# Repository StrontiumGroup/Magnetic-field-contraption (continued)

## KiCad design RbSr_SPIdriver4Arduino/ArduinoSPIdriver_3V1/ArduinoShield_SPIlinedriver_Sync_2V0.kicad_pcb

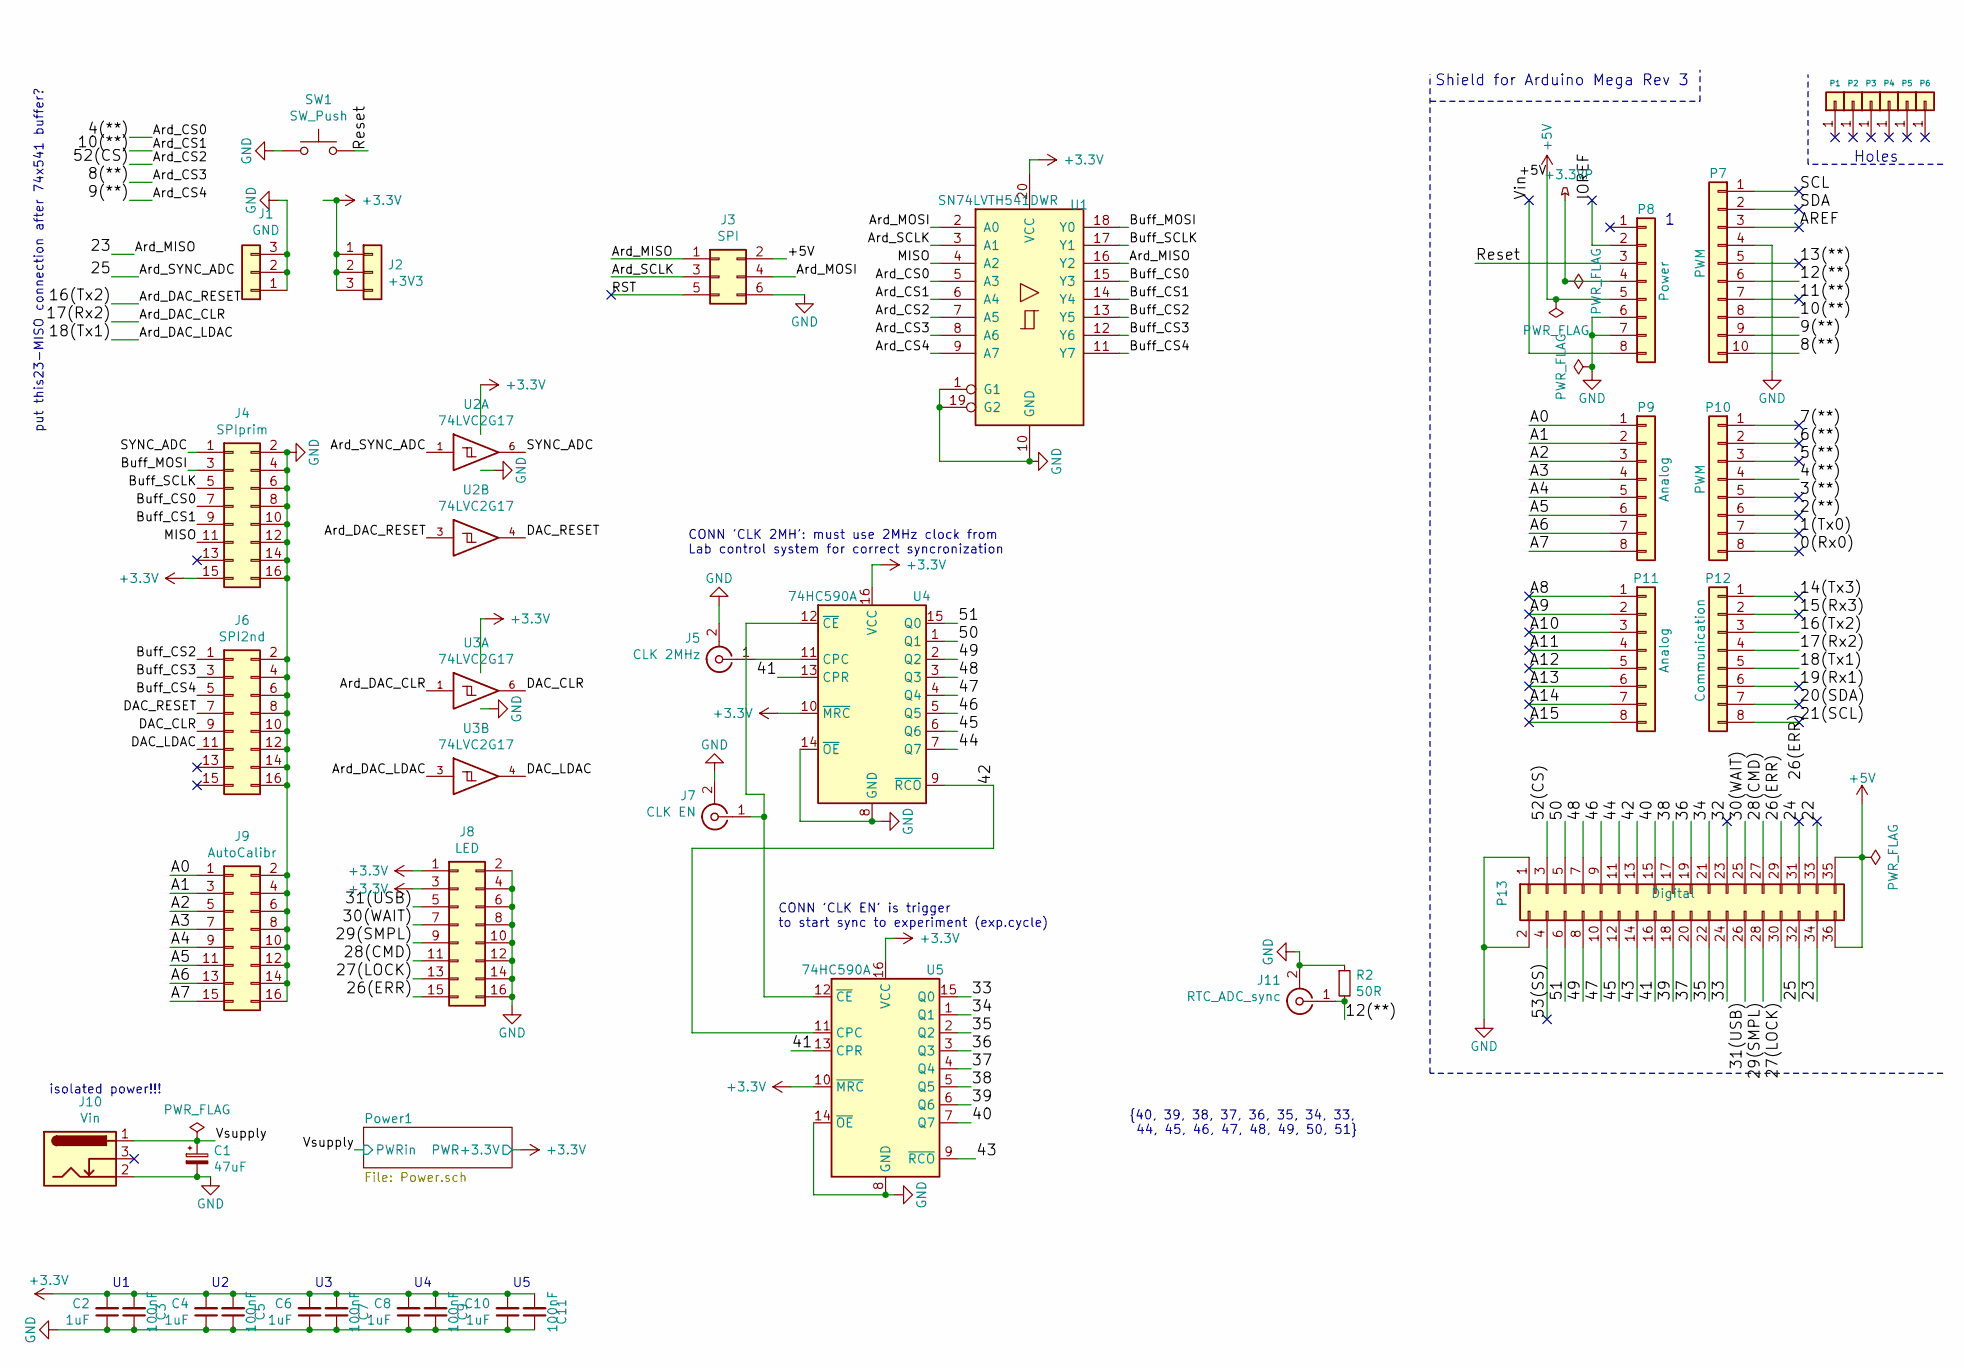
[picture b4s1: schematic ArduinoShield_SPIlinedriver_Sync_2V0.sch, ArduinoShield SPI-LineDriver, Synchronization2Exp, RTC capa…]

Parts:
C1: 47uF; CP_EIA-7343-30_AVX-N; DigiKey 490-ECASD31C476M040KA0CT-ND
C2, C4, C6, C8, C10: 1uF; C_0603_1608Metric; DigiKey 732-7971-1-ND
C3, C5, C7, C9, C11: 100nF; C_0603_1608Metric; DigiKey 732-7989-1-ND
J1: GND; PinSocket_1x03_P2.54mm_Vertical; DigiKey SAM1213-03-ND
J2: +3V3; PinSocket_1x03_P2.54mm_Vertical; DigiKey SAM1213-03-ND
J3: SPI; PinSocket_2x03_P2.54mm_Vertical; DigiKey SAM1204-03-ND
J4: SPIprim; IDC-Header_2x08_P2.54mm_Vertical; DigiKey 609-3641-ND
J5: CLK 2MHz; SMA_Amphenol_132291_Vertical; DigiKey ACX1976-ND
J6: SPI2nd; IDC-Header_2x08_P2.54mm_Vertical; DigiKey 609-3641-ND
J7: CLK EN; SMA_Amphenol_132291_Vertical; DigiKey ACX1976-ND
J8: LED; IDC-Header_2x08_P2.54mm_Vertical; DigiKey 609-3641-ND
J9: AutoCalibr; IDC-Header_2x08_P2.54mm_Vertical; DigiKey 609-3641-ND
J10: Vin; BarrelJack_Wuerth_6941xx301002; DigiKey 732-5930-ND
J11: RTC_ADC_sync; SMA_Amphenol_132291_Vertical; DigiKey ACX1976-ND
P1, P2, P3, P4, P5, P6: CONN_01X01; Arduino_1pin
P7: PWM; Socket_Strip_Arduino_1x10; DigiKey SAM1206-10-ND
P8: Power; Socket_Strip_Arduino_1x08; DigiKey SAM11912-ND
P9, P11: Analog; Socket_Strip_Arduino_1x08; DigiKey SAM11912-ND
P10: PWM; Socket_Strip_Arduino_1x08; DigiKey SAM11912-ND
P12: Communication; Socket_Strip_Arduino_1x08; DigiKey SAM11912-ND
P13: Digital; Socket_Strip_Arduino_2x18; DigiKey SAM1204-18-ND
R2: 50R; R_0603_1608Metric; DigiKey 541-2655-1-ND
SW1: SW_Push; WS-TASV_SwitchTactile_430471035826; DigiKey 430471035826
U1: SN74LVTH541DWR; TSSOP-20_4.4x6.5mm_P0.65mm; DigiKey 296-8729-1-ND
U2, U3: 74LVC2G17; SOT-363_SC-70-6; DigiKey 296-13013-1-ND
U4, U5: 74HC590A; SOIC-16_3.9x9.9mm_P1.27mm; DigiKey 296-17132-1-ND

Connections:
+3.3VP: P8.4
+3V3: C2.2, C3.2, C4.2, C5.2, C6.2, C7.2, C8.2, C9.2, C10.2, C11.2, J2.1, J2.2, J2.3, J4.15, J8.1, J8.3, U1.20 (VCC), U2.5 (VCC), U3.5 (VCC), U4.10 (~MRC), U4.16 (VCC), U5.10 (~MRC), U5.16 (VCC); also elsewhere on the board
+5V: J3.2, P8.5, P13.35, P13.36
/0(Rx0): P10.8
/1(Tx0): P10.7
/2(**): P10.6
/3(**): P10.5
/4(**): P10.4, U1.5 (A3)
/5(**): P10.3
/6(**): P10.2
/7(**): P10.1
/8(**): P7.10, U1.8 (A6)
/9(**): P7.9, U1.9 (A7)
/10(**): P7.8, U1.6 (A4)
/11(**): P7.7
/12(**): J11.1 (In), P7.6, R2.2
/13(**): P7.5
/14(Tx3): P12.1
/15(Rx3): P12.2
/16(Tx2): P12.3, U2.3
/17(Rx2): P12.4, U3.1
/18(Tx1): P12.5, U3.3
/19(Rx1): P12.6
/20(SDA): P12.7
/21(SCL): P12.8
/22: P13.33
/23: J3.1, P13.34, U1.16 (Y2)
/24: P13.31
/25: P13.32, U2.1
/26(ERR): J8.15, P13.29
/27(LOCK): J8.13, P13.30
/28(CMD): J8.11, P13.27
/29(SMPL): J8.9, P13.28
/30(WAIT): J8.7, P13.25
/31(USB): J8.5, P13.26
/32: P13.23
/33: P13.24, U5.15 (Q0)
/34: P13.21, U5.1 (Q1)
/35: P13.22, U5.2 (Q2)
/36: P13.19, U5.3 (Q3)
/37: P13.20, U5.4 (Q4)
/38: P13.17, U5.5 (Q5)
/39: P13.18, U5.6 (Q6)
/40: P13.15, U5.7 (Q7)
/41: P13.16, U4.13 (CPR), U5.13 (CPR)
/42: P13.13, U4.9 (~RCO), U5.11 (CPC)
/43: P13.14, U5.9 (~RCO)
/44: P13.11, U4.7 (Q7)
/45: P13.12, U4.6 (Q6)
/46: P13.9, U4.5 (Q5)
/47: P13.10, U4.4 (Q4)
/48: P13.7, U4.3 (Q3)
/49: P13.8, U4.2 (Q2)
/50: P13.5, U4.1 (Q1)
/51: P13.6, U4.15 (Q0)
/52(CS): P13.3, U1.7 (A5)
/53(SS): P13.4
/A0: J9.1, P9.1
/A1: J9.3, P9.2
/A2: J9.5, P9.3
/A3: J9.7, P9.4
/A4: J9.9, P9.5
/A5: J9.11, P9.6
/A6: J9.13, P9.7
/A7: J9.15, P9.8
/A8: P11.1
/A9: P11.2
/A10: P11.3
/A11: P11.4
/A12: P11.5
/A13: P11.6
/A14: P11.7
/A15: P11.8
/AREF: P7.3
/Ard_MOSI: J3.4, U1.2 (A0)
/Ard_SCLK: J3.3, U1.3 (A1)
/Buff_CS0: J4.7, U1.15 (Y3)
/Buff_CS1: J4.9, U1.14 (Y4)
/Buff_CS2: J6.1, U1.13 (Y5)
/Buff_CS3: J6.3, U1.12 (Y6)
/Buff_CS4: J6.5, U1.11 (Y7)
/Buff_MOSI: J4.3, U1.18 (Y0)
/Buff_SCLK: J4.5, U1.17 (Y1)
/DAC_CLR: J6.9, U3.6
/DAC_LDAC: J6.11, U3.4
/DAC_RESET: J6.7, U2.4
/IOREF: P8.2
/MISO: J4.11, U1.4 (A2)
/RST: J3.5
/Reset: P8.3, SW1.2
/SCL: P7.1
/SDA: P7.2
/SYNC_ADC: J4.1, U2.6
/Vin: P8.8
/Vsupply: C1.1, J10.1; also elsewhere on the board
GND: C1.2, C2.1, C3.1, C4.1, C5.1, C6.1, C7.1, C8.1, C9.1, C10.1, C11.1, J1.1, J1.2, J1.3, J3.6, J4.2, J4.4, J4.6, J4.8, J4.10, J4.12, J4.14, J4.16, J5.2 (Ext), J6.2, J6.4, J6.6, J6.8, J6.10, J6.12, J6.14, J6.16, J7.2 (Ext), J8.2, J8.4, J8.6, J8.8, J8.10, J8.12, J8.14, J8.16, J9.2, J9.4, J9.6, J9.8, J9.10, J9.12, J9.14, J9.16, J10.2, J11.2 (Ext), P7.4, P8.6, P8.7, P13.1, P13.2, R2.1, SW1.1, U1.1 (G1), U1.10 (GND), U1.19 (G2), U2.2 (GND), U3.2 (GND), U4.8 (GND), U4.14 (~OE), U5.8 (GND), U5.14 (~OE); also elsewhere on the board
unnamed: J5.1 (In), U4.11 (CPC)
unnamed: J7.1 (In), U4.12 (~CE), U5.12 (~CE)

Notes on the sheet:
Shield for Arduino Mega Rev 3
Holes
{40, 39, 38, 37, 36, 35, 34, 33, 44, 45, 46, 47, 48, 49, 50, 51}
put this23-MISO connection after 74x541 buffer?
CONN 'CLK 2MH': must use 2MHz clock from Lab control system for correct syncronization
CONN 'CLK EN' is trigger to start sync to experiment (exp.cycle)
isolated power!!!

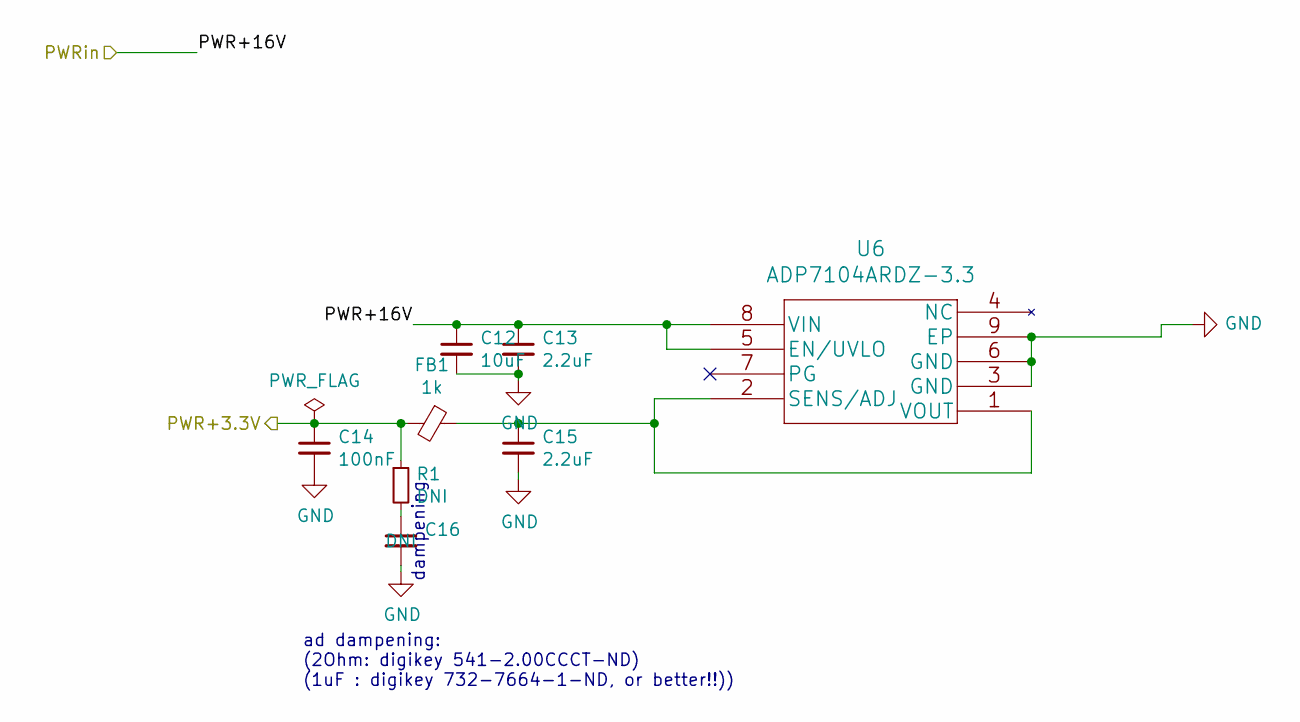
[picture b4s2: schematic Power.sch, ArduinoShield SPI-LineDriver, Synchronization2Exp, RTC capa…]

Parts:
C12: 10uF; C_1206_3216Metric; DigiKey 1276-2876-1-ND
C13, C15: 2.2uF; C_1210_3225Metric; DigiKey 445-6098-1-ND
C14, C16: 100nF; C_0805_2012Metric; DigiKey 732-8080-1-ND
FB1: 1k; L_0805_2012Metric; DigiKey A102197CT-ND
R1: 2R; R_0805_2012Metric; DigiKey 311-2.00CRCT-ND
U6: ADP7104ARDZ-3.3; SOIC-8-1EP_3.9x4.9mm_P1.27mm_EP2.41x3.81mm; DigiKey ADP7104ARDZ-3.3-R7CT-ND

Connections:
+3V3: C14.1, FB1.2, R1.1; also elsewhere on the board
/Vsupply: C12.1, C13.1, U6.5 (EN/UVLO), U6.8 (VIN); also elsewhere on the board
GND: C12.2, C13.2, C14.2, C15.2, C16.2, U6.3 (GND), U6.6 (GND), U6.9 (EP); also elsewhere on the board
unnamed: C15.1, FB1.1, U6.1 (VOUT), U6.2 (SENS/ADJ)
unnamed: C16.1, R1.2

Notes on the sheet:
dampening
ad dampening: (2Ohm: digikey 541-2.00CCCT-ND) (1uF : digikey 732-7664-1-ND, or better!!))

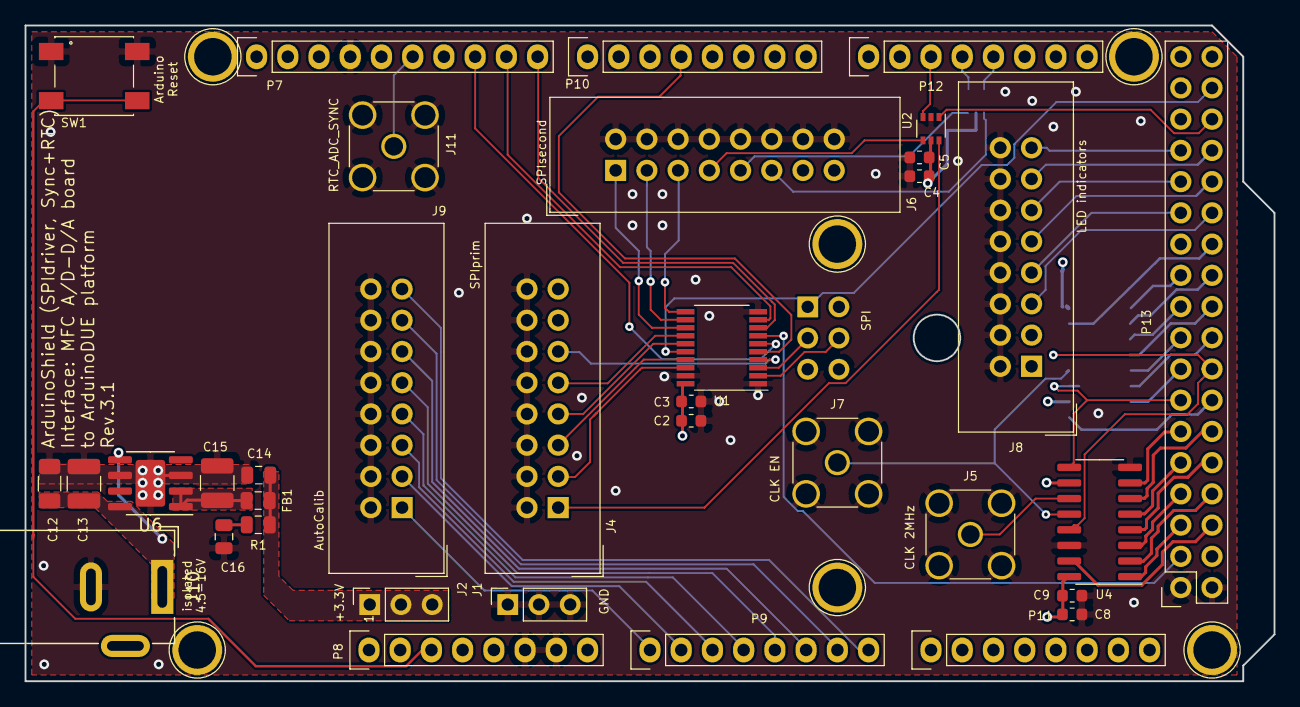
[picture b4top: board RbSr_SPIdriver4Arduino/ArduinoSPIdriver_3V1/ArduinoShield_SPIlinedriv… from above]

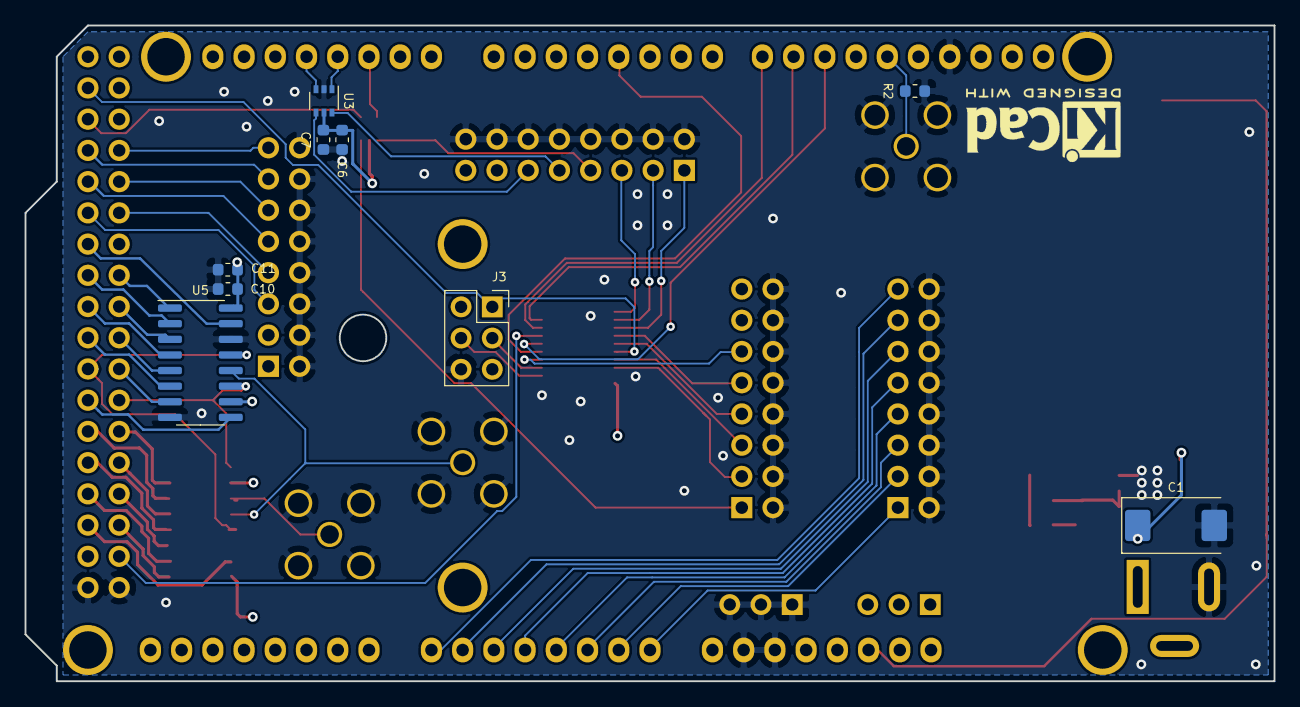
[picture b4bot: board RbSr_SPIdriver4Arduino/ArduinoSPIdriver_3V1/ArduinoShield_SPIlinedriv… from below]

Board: 4 copper layers, 101.6 x 53.3 mm, 50 parts (9 on the bottom side), 67 nets.

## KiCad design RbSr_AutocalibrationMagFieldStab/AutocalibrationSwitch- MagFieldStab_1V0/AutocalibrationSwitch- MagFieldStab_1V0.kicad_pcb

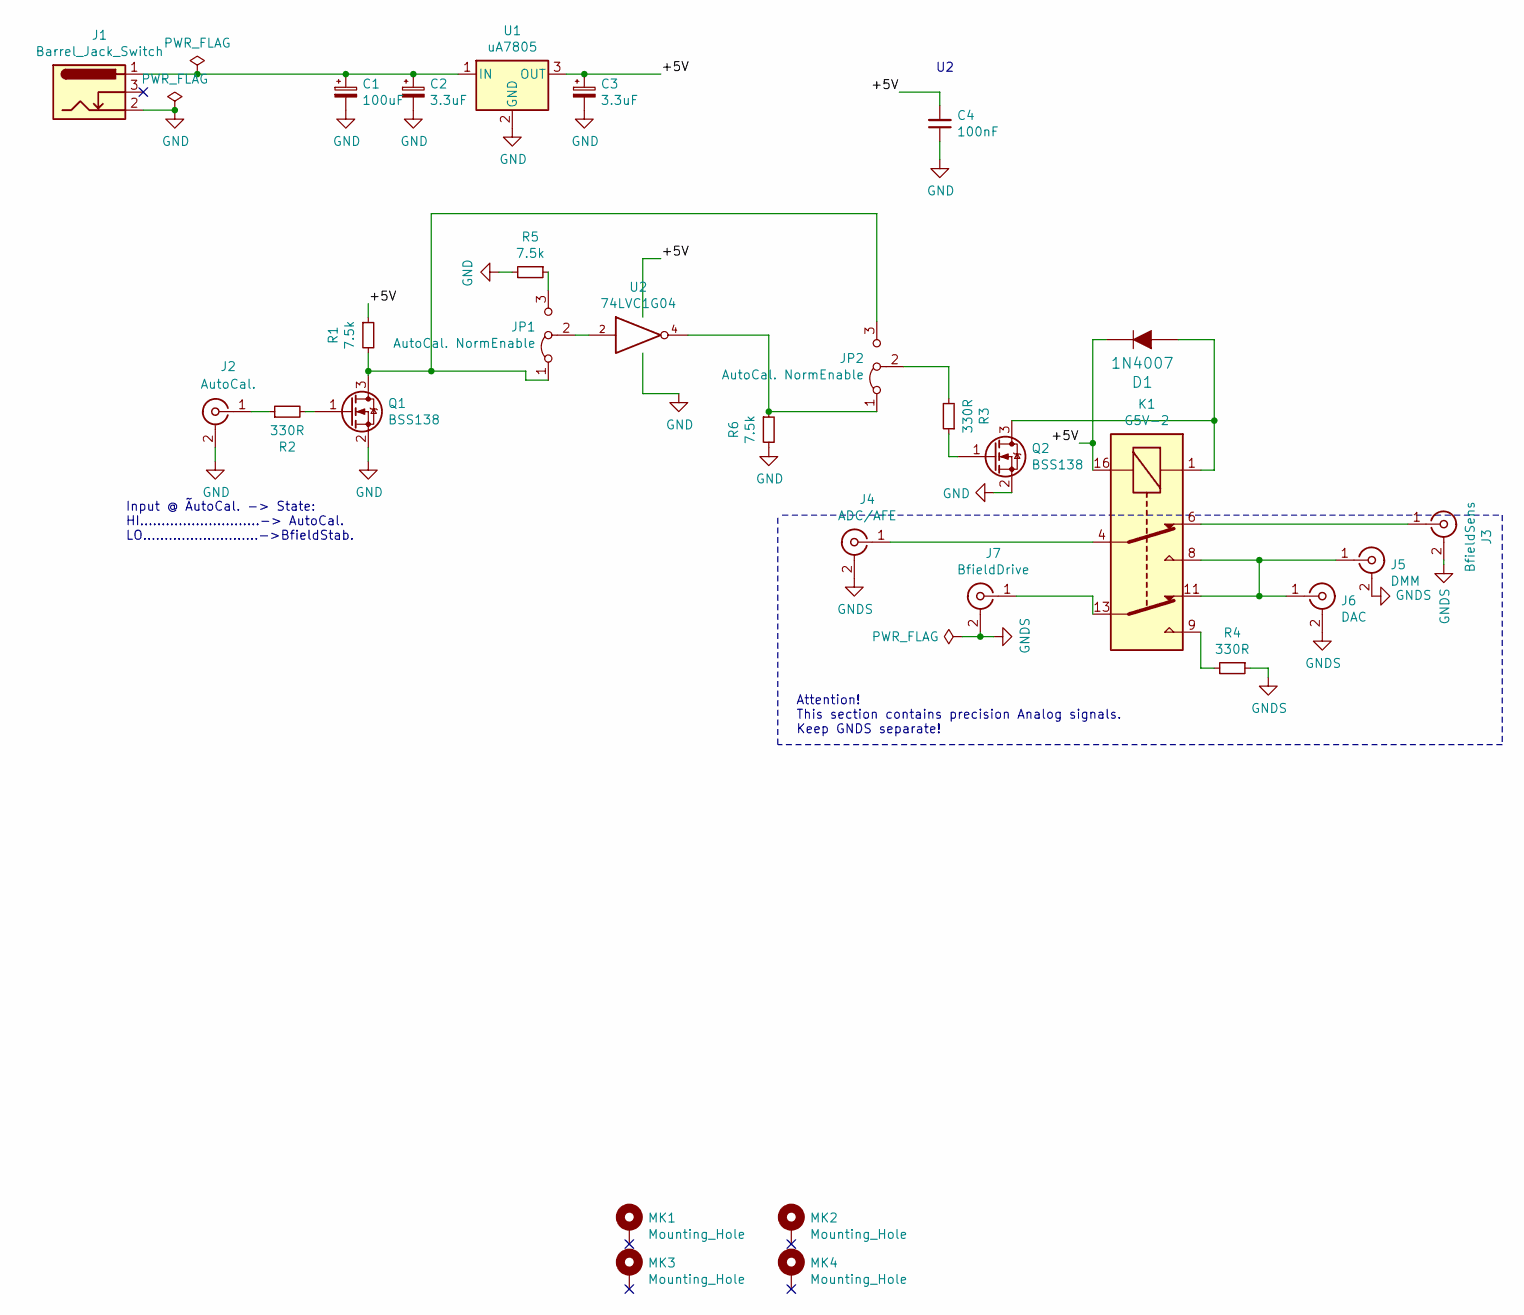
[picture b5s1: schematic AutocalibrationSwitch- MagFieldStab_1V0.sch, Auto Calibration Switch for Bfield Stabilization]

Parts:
C1: 100uF; CP_Radial_D6.3mm_P2.50mm; DigiKey 732-9170-1-ND
C2, C3: 3.3uF; CP_Radial_D5.0mm_P2.50mm; DigiKey P19607CT-ND
C4: 100nF; C_0805_2012Metric; DigiKey 732-8061-1-ND
D1: 1N4007; DO-41; MPN 1N4007-T; Digi-Key 1N4007DICT-ND
J1: Barrel_Jack_Switch; BarrelJack_Wuerth_6941xx301002; DigiKey 732-5930-ND
J2: AutoCal.; SMA_Molex_73251-2200_Horizontal; DigiKey WM26450-ND
J3: BfieldSens; SMA_Molex_73251-2200_Horizontal; DigiKey WM26450-ND
J4: ADC/AFE; SMA_Molex_73251-2200_Horizontal; DigiKey WM26450-ND
J5: DMM; SMA_Amphenol_132291_Vertical; DigiKey ACX1230-ND
J6: DAC; SMA_Molex_73251-2200_Horizontal; DigiKey WM26450-ND
J7: BfieldDrive; SMA_Molex_73251-2200_Horizontal; DigiKey WM26450-ND
JP1, JP2: AutoCal. NormEnable; SolderJumper-3_P2.0mm_Open_TrianglePad1.0x1.5mm_NumberLabels
K1: G5V-2; Relay_DPDT_Omron_G5V-2; DigiKey Z2931-ND
MK1, MK2, MK3, MK4: Mounting_Hole; MountingHole_3.2mm_M3_ISO7380
Q1, Q2: BSS138; SOT-23; DigiKey 1727-1142-1-ND
R1, R5, R6: 7.5k; R_0805_2012Metric; DigiKey P7.5KACT-ND
R2, R3, R4: 330R; R_0805_2012Metric; DigiKey A129743CT-ND
U1: uA7805; TO-220-3_Vertical; DigiKey 296-39515-5-ND
U2: 74LVC1G04; SOT-353_SC-70-5; DigiKey 296-35933-1-ND

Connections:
GND: C1.2, C2.2, C3.2, C4.1, J1.2, J2.2 (Ext), Q1.2 (S), Q2.2 (S), R5.2, R6.2, U1.2 (GND), U2.3 (GND)
GNDS: J3.2 (Ext), J4.2 (Ext), J5.2 (Ext), J6.2 (Ext), J7.2 (Ext), R4.1
unnamed: C1.1, C2.1, J1.1, U1.1 (IN)
unnamed: D1.A, K1.1, Q2.3 (D)
unnamed: J2.1 (In), R2.1
unnamed: J3.1 (In), K1.6
unnamed: J4.1 (In), K1.4
unnamed: J5.1 (In), J6.1 (In), K1.8, K1.11
unnamed: J7.1 (In), K1.13
unnamed: JP1.1 (A), JP2.3 (B), Q1.3 (D), R1.2
unnamed: JP1.2 (C), U2.2
unnamed: JP1.3 (B), R5.1
unnamed: JP2.1 (A), R6.1, U2.4
unnamed: JP2.2 (C), R3.2
unnamed: K1.9, R4.2
unnamed: Q1.1 (G), R2.2
unnamed: Q2.1 (G), R3.1
VCC: C3.1, C4.2, D1.K, K1.16, R1.1, U1.3 (OUT), U2.5 (VCC)

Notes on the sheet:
Attention! This section contains precision Analog signals. Keep GNDS separate!
Input @ ÃutoCal. -> State: HI............................-> AutoCal. LO...........................->BfieldStab.

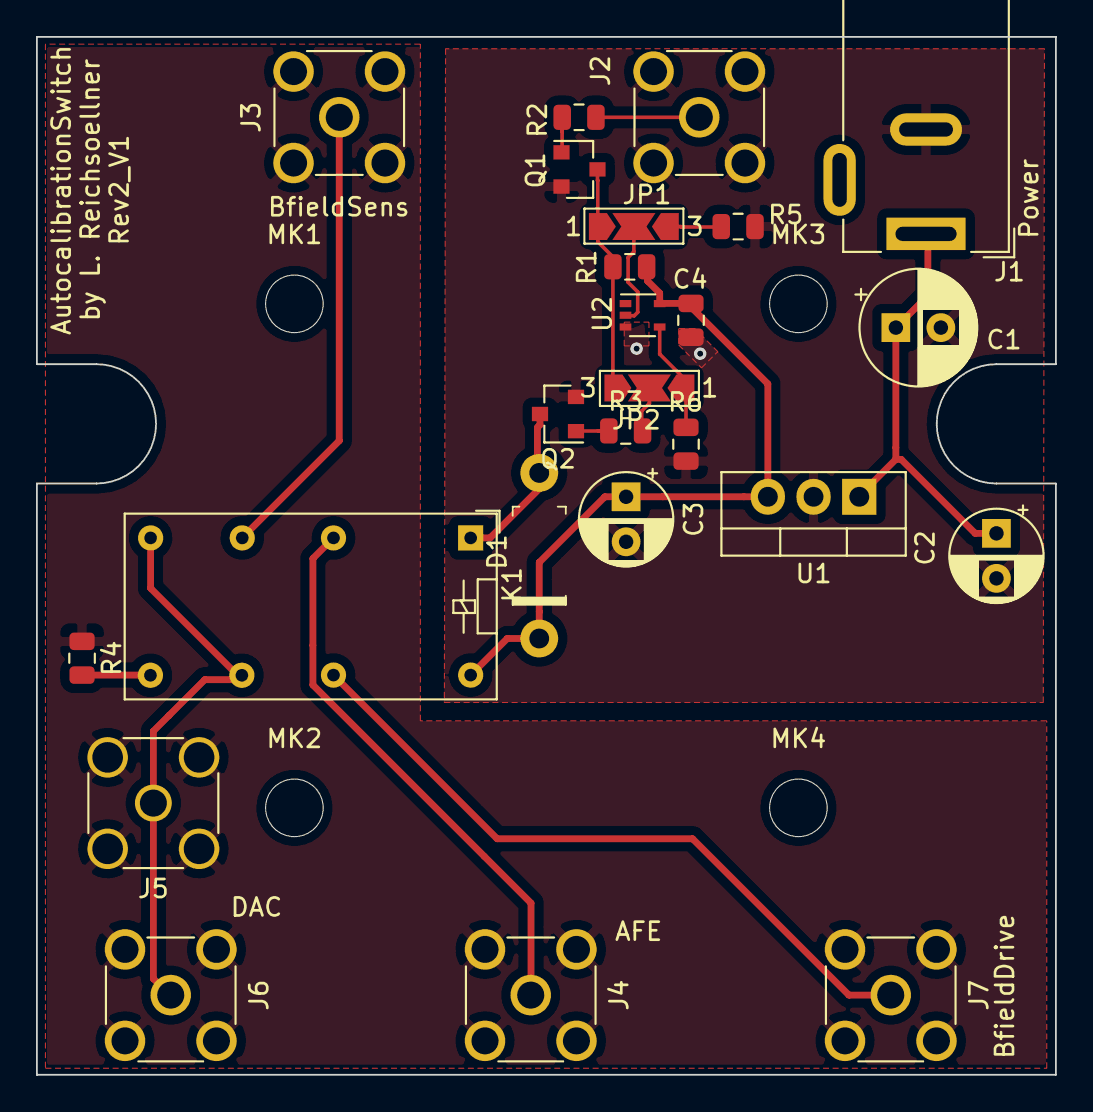
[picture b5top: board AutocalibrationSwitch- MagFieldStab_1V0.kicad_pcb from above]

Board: 2 copper layers, 56.6 x 57.7 mm, 29 parts (0 on the bottom side), 18 nets.

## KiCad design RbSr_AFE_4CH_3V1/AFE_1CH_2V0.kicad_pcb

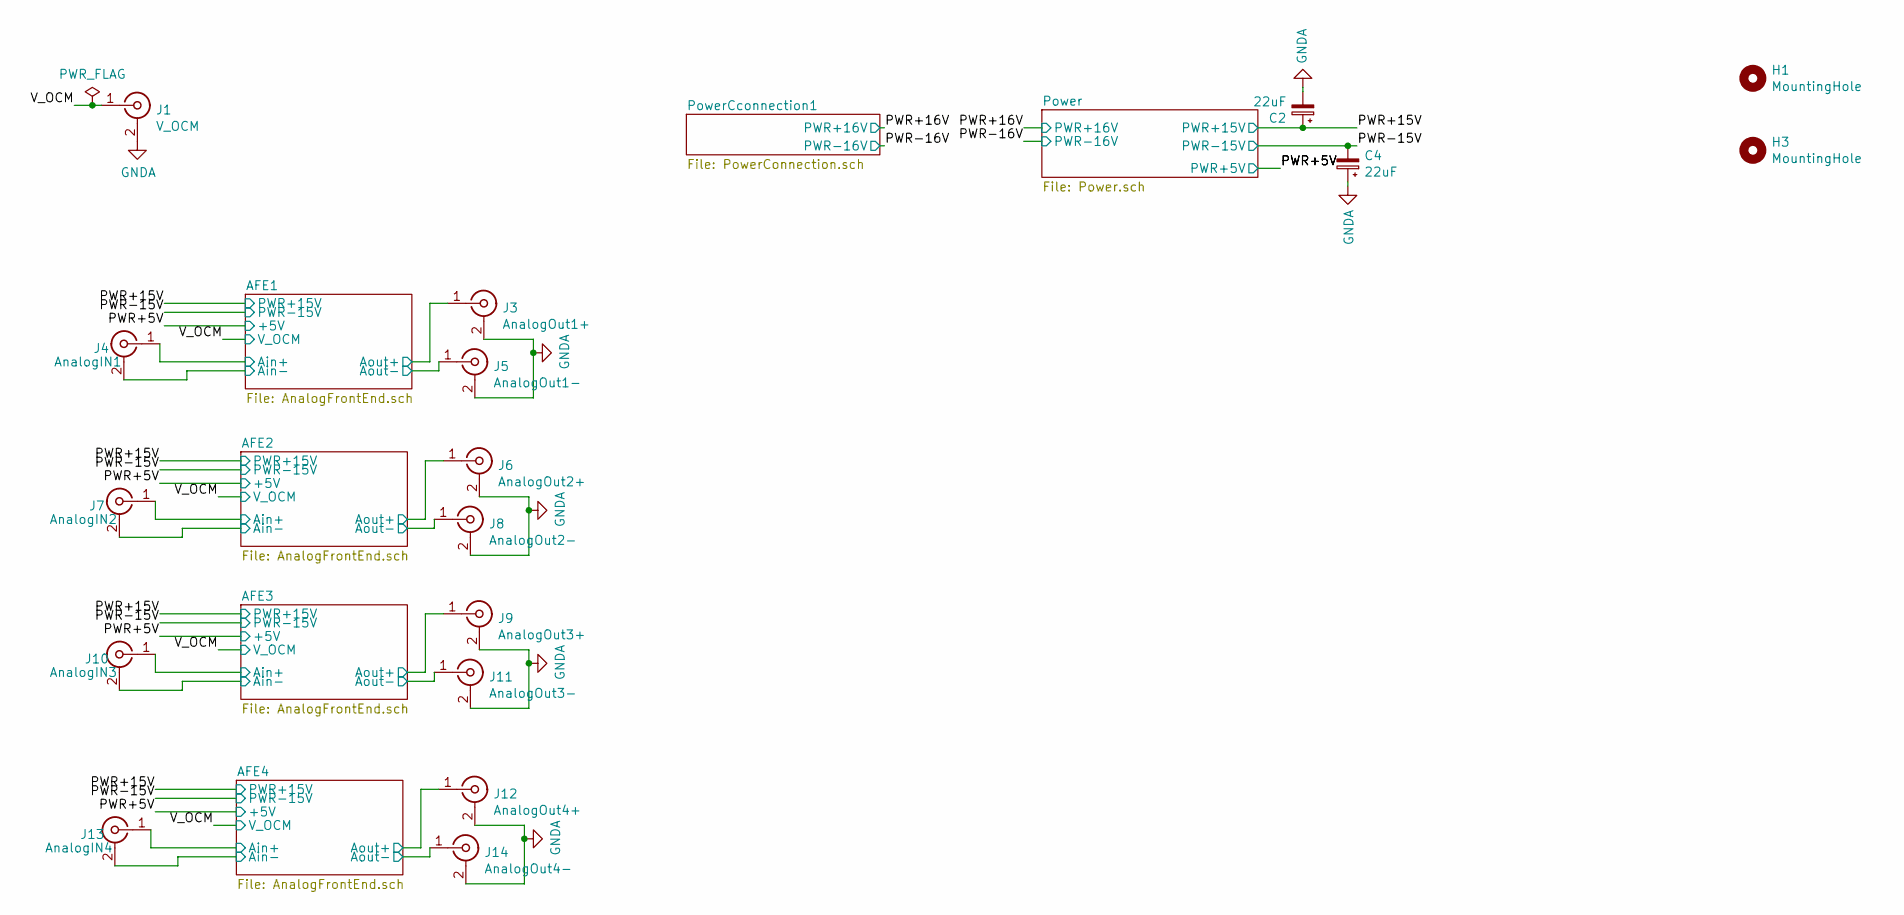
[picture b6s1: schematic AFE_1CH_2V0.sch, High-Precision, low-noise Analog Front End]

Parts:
C2, C4: 22uF; CP_Radial_D5.0mm_P2.00mm; DigiKey 732-9317-1-ND
H1, H3: MountingHole; MountingHole_2.7mm_M2.5_Pad
J1: V_OCM; RF_SMB_jack_Vertical; DigiKey A102025-ND
J3: AnalogOut1+; RF_SMB_jack_Vertical; DigiKey A102025-ND
J4: AnalogIN1; BNC_JACK_hor_50OHM_PCB; DigiKey A97555-ND
J5: AnalogOut1-; RF_SMB_jack_Vertical; DigiKey A102025-ND
J6: AnalogOut2+; RF_SMB_jack_Vertical; DigiKey A102025-ND
J7: AnalogIN2; BNC_JACK_hor_50OHM_PCB; DigiKey A97555-ND
J8: AnalogOut2-; RF_SMB_jack_Vertical; DigiKey A102025-ND
J9: AnalogOut3+; RF_SMB_jack_Vertical; DigiKey A102025-ND
J10: AnalogIN3; BNC_JACK_hor_50OHM_PCB; DigiKey A97555-ND
J11: AnalogOut3-; RF_SMB_jack_Vertical; DigiKey A102025-ND
J12: AnalogOut4+; RF_SMB_jack_Vertical; DigiKey A102025-ND
J13: AnalogIN4; BNC_JACK_hor_50OHM_PCB; DigiKey A97555-ND
J14: AnalogOut4-; RF_SMB_jack_Vertical; DigiKey A102025-ND

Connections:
/AFE1/Ain+: J4.1 (In); also elsewhere on the board
/AFE1/Ain-: J4.2 (Ext); also elsewhere on the board
/AFE1/Aout+: J3.1 (In); also elsewhere on the board
/AFE1/Aout-: J5.1 (In); also elsewhere on the board
/AFE2/Ain+: J7.1 (In); also elsewhere on the board
/AFE2/Ain-: J7.2 (Ext); also elsewhere on the board
/AFE2/Aout+: J6.1 (In); also elsewhere on the board
/AFE2/Aout-: J8.1 (In); also elsewhere on the board
/AFE3/Ain+: J10.1 (In); also elsewhere on the board
/AFE3/Ain-: J10.2 (Ext); also elsewhere on the board
/AFE3/Aout+: J9.1 (In); also elsewhere on the board
/AFE3/Aout-: J11.1 (In); also elsewhere on the board
/AFE4/Ain+: J13.1 (In); also elsewhere on the board
/AFE4/Ain-: J13.2 (Ext); also elsewhere on the board
/AFE4/Aout+: J12.1 (In); also elsewhere on the board
/AFE4/Aout-: J14.1 (In); also elsewhere on the board
/PWR+15V: C2.1; also elsewhere on the board
/PWR-15V: C4.2; also elsewhere on the board
/V_OCM: J1.1 (In); also elsewhere on the board
GND: C2.2, C4.1, J1.2 (Ext), J3.2 (Ext), J5.2 (Ext), J6.2 (Ext), J8.2 (Ext), J9.2 (Ext), J11.2 (Ext), J12.2 (Ext), J14.2 (Ext); also elsewhere on the board

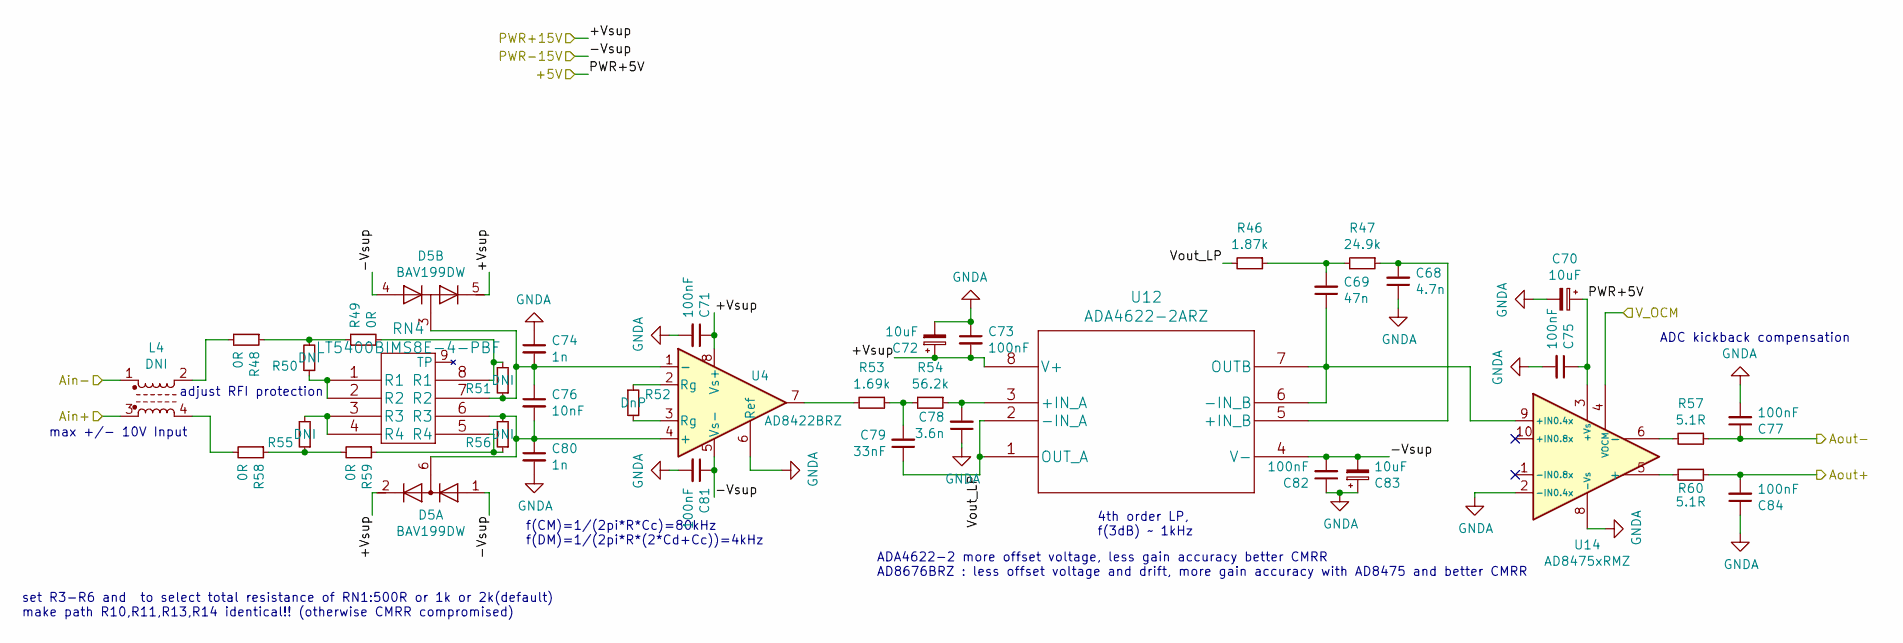
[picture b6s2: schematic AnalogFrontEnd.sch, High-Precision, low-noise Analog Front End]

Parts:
C17: 4.7n; C_0603_1608Metric; DigiKey 399-17408-1-ND
C18: 47n; C_0805_2012Metric; DigiKey 399-8092-1-ND
C19, C21, C32: 10uF; CP_Elec_4x5.4; DigiKey 399-6695-1-ND
C20, C22, C24, C26, C30, C31, C33: 100nF; C_0805_2012Metric; DigiKey 732-8080-1-ND
C23, C29: 1n; C_0805_2012Metric; DigiKey 1276-1020-1-ND
C25: 10nF; C_0805_2012Metric; DigiKey 1276-1245-1-ND
C27: 3.6n; C_0603_1608Metric; DigiKey 399-14515-1-ND
C28: 33nF; C_0805_2012Metric; DigiKey 445-7523-1-ND
D2: BAV199DW; SOT-363_SC-70-6; DigiKey BAV199DW-FDITR-ND
L1: 6.5mH; L_CommonMode_Wuerth_WE-SL2; DigiKey 732-1488-6-ND
R1: 1.87k; R_0603_1608Metric; DigiKey 541-2003-1-ND
R2: 24.9k; R_0603_1608Metric; DigiKey TNP24.9KAACT-ND
R3, R4, R5, R6, R10, R11, R13, R14: 0R; R_0603_1608Metric; DigiKey 311-0.0GRCT-ND
R7: R; R_0805_2012Metric
R8: 1.69k; R_0603_1608Metric; DigiKey 541-3611-1-ND
R9: 56.2k; R_0603_1608Metric; DigiKey 541-3694-1-ND
R12, R15: 5.1R; R_0805_2012Metric; DigiKey 541-5.10CCCT-ND
RN1: LT5400BIMS8E-4-PBF; MSOP-8-1EP_3x3mm_P0.65mm_EP1.68x1.88mm; DigiKey LT5400BIMS8E-4#PBF-ND
U3: ADA4622-2ARZ; SOIC-8_3.9x4.9mm_P1.27mm; DigiKey ADA4622-2BRZ-R7CT-ND
U5: AD8475xRMZ; MSOP-10_3x3mm_P0.5mm; DigiKey AD8475ARMZ-ND
U13: AD8422BRZ; SOIC-8_3.9x4.9mm_P1.27mm; DigiKey AD8422ARZ-R7CT-ND

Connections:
/AFE1/Ain+: L1.3; also elsewhere on the board
/AFE1/Ain-: L1.1; also elsewhere on the board
/AFE1/Aout+: C33.2, R15.1; also elsewhere on the board
/AFE1/Aout-: C26.1, R12.1; also elsewhere on the board
/AFE1/Vout_LP: C28.1, R1.2, U3.1 (OUT_A), U3.2 (-IN_A)
/PWR+5V: C19.1, C24.1, U5.3 (+Vs); also elsewhere on the board
/PWR+15V: C20.1, C21.1, C22.2, D2.2 (K2), D2.5 (K4), U3.8 (V+), U13.8 (Vs+); also elsewhere on the board
/PWR-15V: C30.1, C31.2, C32.2, D2.1 (A1), D2.4 (A3), U3.4 (V-), U13.5 (Vs-); also elsewhere on the board
/V_OCM: U5.4 (VOCM); also elsewhere on the board
GND: C17.1, C19.2, C20.2, C21.2, C22.1, C23.1, C24.2, C26.2, C27.1, C29.2, C30.2, C31.1, C32.1, C33.1, U5.2 (-IN0.4x), U5.8 (-Vs), U13.6 (Ref); also elsewhere on the board
unnamed: C17.2, R2.1, U3.5 (+IN_B)
unnamed: C18.1, U3.6 (-IN_B), U3.7 (OUTB), U5.9 (+IN0.4x)
unnamed: C18.2, R1.1, R2.2
unnamed: C23.2, C25.1, D2.3 (K1A2), R6.1, RN1.7 (R2), U13.1 (-)
unnamed: C25.2, C29.1, D2.6 (K3A4), R11.2, RN1.6 (R3), U13.4 (+)
unnamed: C27.2, R9.1, U3.3 (+IN_A)
unnamed: C28.2, R8.1, R9.2
unnamed: L1.2, R3.2
unnamed: L1.4, R13.2
unnamed: R3.1, R4.1, R5.2
unnamed: R4.2, R6.2, RN1.8 (R1)
unnamed: R5.1, RN1.1 (R1), RN1.2 (R2)
unnamed: R7.1, U13.2 (Rg)
unnamed: R7.2, U13.3 (Rg)
unnamed: R8.2, U13.7
unnamed: R10.1, R13.1, R14.2
unnamed: R10.2, RN1.3 (R3), RN1.4 (R4)
unnamed: R11.1, R14.1, RN1.5 (R4)
unnamed: R12.2, U5.6 (-)
unnamed: R15.2, U5.5 (+)

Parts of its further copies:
C34, C51, C68: 4.7n; C_0603_1608Metric; DigiKey 399-17408-1-ND
C35, C52, C69: 47n; C_0805_2012Metric; DigiKey 399-8092-1-ND
C36, C38, C49, C53, C55, C66, C70, C72, C83: 10uF; CP_Elec_4x5.4; DigiKey 399-6695-1-ND
C37, C39, C41, C43, C47, C48, C50, C54, C56, C58, C60, C64, C65, C67, C71, C73, C75, C77, C81, C82, C84: 100nF; C_0805_2012Metric; DigiKey 732-8080-1-ND
C40, C46, C57, C63, C74, C80: 1n; C_0805_2012Metric; DigiKey 1276-1020-1-ND
C42, C59, C76: 10nF; C_0805_2012Metric; DigiKey 1276-1245-1-ND
C44, C61, C78: 3.6n; C_0603_1608Metric; DigiKey 399-14515-1-ND
C45, C62, C79: 33nF; C_0805_2012Metric; DigiKey 445-7523-1-ND
D3, D4, D5: BAV199DW; SOT-363_SC-70-6; DigiKey BAV199DW-FDITR-ND
L2, L3, L4: 6.5mH; L_CommonMode_Wuerth_WE-SL2; DigiKey 732-1488-6-ND
R16, R31, R46: 1.87k; R_0603_1608Metric; DigiKey 541-2003-1-ND
R17, R32, R47: 24.9k; R_0603_1608Metric; DigiKey TNP24.9KAACT-ND
R18, R19, R20, R21, R25, R26, R28, R29, R33, R34, R35, R36, R40, R41, R43, R44, R48, R49, R50, R51, R55, R56, R58, R59: 0R; R_0603_1608Metric; DigiKey 311-0.0GRCT-ND
R22, R37, R52: R; R_0805_2012Metric
R23, R38, R53: 1.69k; R_0603_1608Metric; DigiKey 541-3611-1-ND
R24, R39, R54: 56.2k; R_0603_1608Metric; DigiKey 541-3694-1-ND
R27, R30, R42, R45, R57, R60: 5.1R; R_0805_2012Metric; DigiKey 541-5.10CCCT-ND
RN2, RN3, RN4: LT5400BIMS8E-4-PBF; MSOP-8-1EP_3x3mm_P0.65mm_EP1.68x1.88mm; DigiKey LT5400BIMS8E-4#PBF-ND
U4, U7, U10: AD8422BRZ; SOIC-8_3.9x4.9mm_P1.27mm; DigiKey AD8422ARZ-R7CT-ND
U6, U9, U12: ADA4622-2ARZ; SOIC-8_3.9x4.9mm_P1.27mm; DigiKey ADA4622-2BRZ-R7CT-ND
U8, U11, U14: AD8475xRMZ; MSOP-10_3x3mm_P0.5mm; DigiKey AD8475ARMZ-ND

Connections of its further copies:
/AFE2/Ain+: L2.3; also elsewhere on the board
/AFE2/Ain-: L2.1; also elsewhere on the board
/AFE2/Aout+: C50.2, R30.1; also elsewhere on the board
/AFE2/Aout-: C43.1, R27.1; also elsewhere on the board
/AFE2/Vout_LP: C45.1, R16.2, U6.1 (OUT_A), U6.2 (-IN_A)
/AFE3/Ain+: L3.3; also elsewhere on the board
/AFE3/Ain-: L3.1; also elsewhere on the board
/AFE3/Aout+: C67.2, R45.1; also elsewhere on the board
/AFE3/Aout-: C60.1, R42.1; also elsewhere on the board
/AFE3/Vout_LP: C62.1, R31.2, U9.1 (OUT_A), U9.2 (-IN_A)
/AFE4/Ain+: L4.3; also elsewhere on the board
/AFE4/Ain-: L4.1; also elsewhere on the board
/AFE4/Aout+: C84.2, R60.1; also elsewhere on the board
/AFE4/Aout-: C77.1, R57.1; also elsewhere on the board
/AFE4/Vout_LP: C79.1, R46.2, U12.1 (OUT_A), U12.2 (-IN_A)
/PWR+5V: C36.1, C41.1, C53.1, C58.1, C70.1, C75.1, U8.3 (+Vs), U11.3 (+Vs), U14.3 (+Vs); also elsewhere on the board
/PWR+15V: C37.1, C38.1, C39.2, C54.1, C55.1, C56.2, C71.1, C72.1, C73.2, D3.2 (K2), D3.5 (K4), D4.2 (K2), D4.5 (K4), D5.2 (K2), D5.5 (K4), U4.8 (Vs+), U6.8 (V+), U7.8 (Vs+), U9.8 (V+), U10.8 (Vs+), U12.8 (V+); also elsewhere on the board
/PWR-15V: C47.1, C48.2, C49.2, C64.1, C65.2, C66.2, C81.1, C82.2, C83.2, D3.1 (A1), D3.4 (A3), D4.1 (A1), D4.4 (A3), D5.1 (A1), D5.4 (A3), U4.5 (Vs-), U6.4 (V-), U7.5 (Vs-), U9.4 (V-), U10.5 (Vs-), U12.4 (V-); also elsewhere on the board
/V_OCM: U8.4 (VOCM), U11.4 (VOCM), U14.4 (VOCM); also elsewhere on the board
GND: C34.1, C36.2, C37.2, C38.2, C39.1, C40.1, C41.2, C43.2, C44.1, C46.2, C47.2, C48.1, C49.1, C50.1, C51.1, C53.2, C54.2, C55.2, C56.1, C57.1, C58.2, C60.2, C61.1, C63.2, C64.2, C65.1, C66.1, C67.1, C68.1, C70.2, C71.2, C72.2, C73.1, C74.1, C75.2, C77.2, C78.1, C80.2, C81.2, C82.1, C83.1, C84.1, U4.6 (Ref), U7.6 (Ref), U8.2 (-IN0.4x), U8.8 (-Vs), U10.6 (Ref), U11.2 (-IN0.4x), U11.8 (-Vs), U14.2 (-IN0.4x), U14.8 (-Vs); also elsewhere on the board
unnamed: C34.2, R17.1, U6.5 (+IN_B)
unnamed: C35.1, U6.6 (-IN_B), U6.7 (OUTB), U8.9 (+IN0.4x)
unnamed: C35.2, R16.1, R17.2
unnamed: C40.2, C42.1, D3.3 (K1A2), R21.1, RN2.7 (R2), U7.1 (-)
unnamed: C42.2, C46.1, D3.6 (K3A4), R26.2, RN2.6 (R3), U7.4 (+)
unnamed: C44.2, R24.1, U6.3 (+IN_A)
unnamed: C45.2, R23.1, R24.2
unnamed: C51.2, R32.1, U9.5 (+IN_B)
unnamed: C52.1, U9.6 (-IN_B), U9.7 (OUTB), U11.9 (+IN0.4x)
unnamed: C52.2, R31.1, R32.2
unnamed: C57.2, C59.1, D4.3 (K1A2), R36.1, RN3.7 (R2), U10.1 (-)
unnamed: C59.2, C63.1, D4.6 (K3A4), R41.2, RN3.6 (R3), U10.4 (+)
unnamed: C61.2, R39.1, U9.3 (+IN_A)
unnamed: C62.2, R38.1, R39.2
unnamed: C68.2, R47.1, U12.5 (+IN_B)
unnamed: C69.1, U12.6 (-IN_B), U12.7 (OUTB), U14.9 (+IN0.4x)
unnamed: C69.2, R46.1, R47.2
unnamed: C74.2, C76.1, D5.3 (K1A2), R51.1, RN4.7 (R2), U4.1 (-)
unnamed: C76.2, C80.1, D5.6 (K3A4), R56.2, RN4.6 (R3), U4.4 (+)
unnamed: C78.2, R54.1, U12.3 (+IN_A)
unnamed: C79.2, R53.1, R54.2
unnamed: L2.2, R18.2
unnamed: L2.4, R28.2
unnamed: L3.2, R33.2
unnamed: L3.4, R43.2
unnamed: L4.2, R48.2
unnamed: L4.4, R58.2
unnamed: R18.1, R19.1, R20.2
unnamed: R19.2, R21.2, RN2.8 (R1)
unnamed: R20.1, RN2.1 (R1), RN2.2 (R2)
unnamed: R22.1, U7.2 (Rg)
unnamed: R22.2, U7.3 (Rg)
unnamed: R23.2, U7.7
unnamed: R25.1, R28.1, R29.2
unnamed: R25.2, RN2.3 (R3), RN2.4 (R4)
unnamed: R26.1, R29.1, RN2.5 (R4)
unnamed: R27.2, U8.6 (-)
unnamed: R30.2, U8.5 (+)
unnamed: R33.1, R34.1, R35.2
unnamed: R34.2, R36.2, RN3.8 (R1)
unnamed: R35.1, RN3.1 (R1), RN3.2 (R2)
unnamed: R37.1, U10.2 (Rg)
unnamed: R37.2, U10.3 (Rg)
unnamed: R38.2, U10.7
unnamed: R40.1, R43.1, R44.2
unnamed: R40.2, RN3.3 (R3), RN3.4 (R4)
unnamed: R41.1, R44.1, RN3.5 (R4)
unnamed: R42.2, U11.6 (-)
unnamed: R45.2, U11.5 (+)
unnamed: R48.1, R49.1, R50.2
unnamed: R49.2, R51.2, RN4.8 (R1)
unnamed: R50.1, RN4.1 (R1), RN4.2 (R2)
unnamed: R52.1, U4.2 (Rg)
unnamed: R52.2, U4.3 (Rg)
unnamed: R53.2, U4.7
unnamed: R55.1, R58.1, R59.2
unnamed: R55.2, RN4.3 (R3), RN4.4 (R4)
unnamed: R56.1, R59.1, RN4.5 (R4)
unnamed: R57.2, U14.6 (-)
unnamed: R60.2, U14.5 (+)

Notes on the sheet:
max +/- 10V Input
adjust RFI protection
ADC kickback compensation
f(CM)=1/(2pi*R*Cc)=80kHz f(DM)=1/(2pi*R*(2*Cd+Cc))=4kHz
set R3-R6 and to select total resistance of RN1:500R or 1k or 2k(default) make path R10,R11,R13,R14 identical!! (otherwise CMRR compromised)
4th order LP, f(3dB) ~~ 1kHz
ADA4622-2 more offset voltage, less gain accuracy better CMRR AD8676BRZ : less offset voltage and drift, more gain accuracy with AD8475 and better CMRR
